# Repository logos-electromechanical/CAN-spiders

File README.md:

# CAN-spiders
A set of small single-function CAN nodes

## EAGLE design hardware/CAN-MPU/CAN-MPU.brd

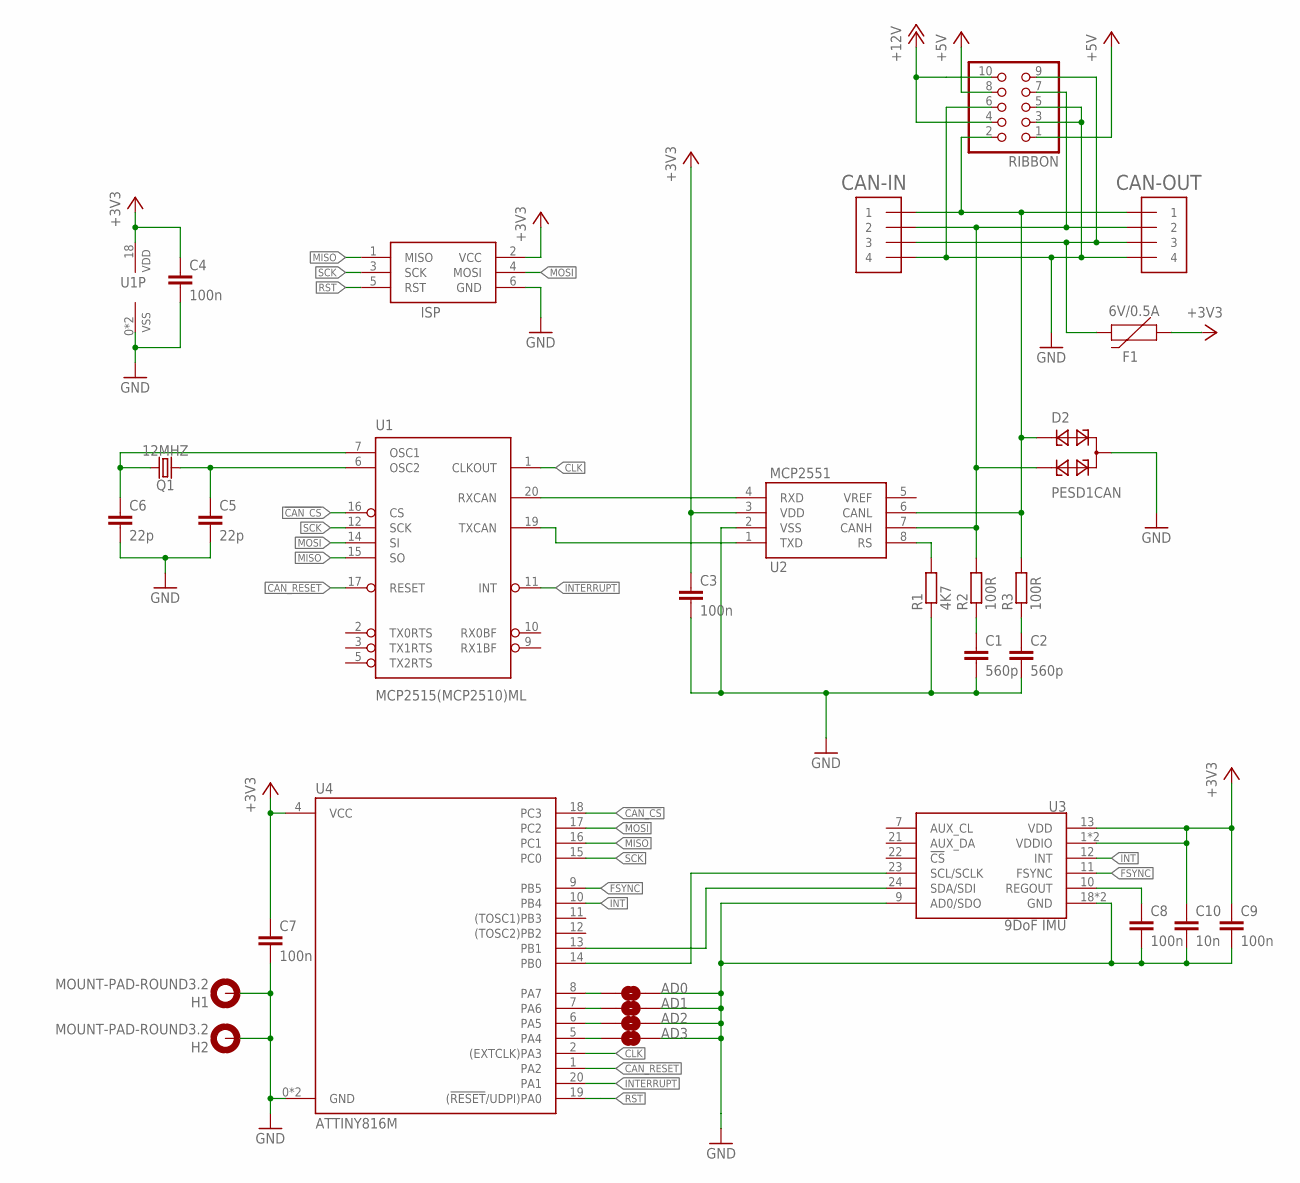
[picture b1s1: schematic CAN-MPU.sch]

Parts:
AD0, AD1, AD2, AD3: JUMPER-SMT_2_NO_SILK; SMT-JUMPER_2_NO_SILK
C1, C2: 560p; C0603
C3, C4, C7, C8, C9: 100n; C0603
C5, C6: 22p; C0603
C10: 10n; C0603
CAN-IN: STRAWSON_EAGLE_LIB_JST_SH_4; STRAWSON_EAGLE_LIB_JST_SH_4_SMD
CAN-OUT: STRAWSON_EAGLE_LIB_JST_SH_4; STRAWSON_EAGLE_LIB_JST_SH_4_SMD
D2: PESD1CAN; SOT23
F1: 6V/0.5A; 1206
H1, H2: MOUNT-PAD-ROUND3.2; 3,2-PAD
ISP: AVRISP-6; AVRISP
Q1: 12MHZ; CRYSTAL-SMD-3.2X1.5MM
R1: 4K7; R0603
R2, R3: 100R; R0603
RIBBON: PINHD-2X5_2.54-SMD; 2X05SMD
U1: MCP2515(MCP2510)ML; QFN20
U2: MCP2551; SO08
U3: 9DoF IMU; QFN24-3X3
U4: ATTINY816M; QFN20

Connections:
!CAN_CS!: U1.16 (CS), U4.18 (PC3)
+3V3: C3.1, C4.1, C7.1, C9.1, C10.1, F1.1, ISP.2 (VCC), U1.18 (VDD), U2.3 (VDD), U3.1 (VDDIO), U3.8 (VDDIO), U3.13 (VDD), U4.4 (VCC)
+5V: RIBBON.1, RIBBON.8
+12V: RIBBON.4, RIBBON.10
CAN_RESET: U1.17 (RESET), U4.1 (PA2)
CLK: U1.1 (CLKOUT), U4.2 ((EXTCLK)PA3)
FSYNC: U3.11 (FSYNC), U4.9 (PB5)
GND: AD0.2, AD1.2, AD2.2, AD3.2, C1.2, C2.2, C3.2, C4.2, C5.2, C6.2, C7.2, C8.2, C9.2, C10.2, CAN-IN.4, CAN-OUT.4, D2.3, H1.B3,2, H2.B3,2, ISP.6 (GND), R1.1, RIBBON.3, RIBBON.5, RIBBON.6, U1.0 (VSS), U1.8 (VSS), U2.2 (VSS), U3.9 (AD0/SDO), U3.18 (GND), U3.20 (GND), U4.0 (GND), U4.3 (GND)
INT: U3.12 (INT), U4.10 (PB4)
INTERRUPT: U1.11 (INT), U4.20 (PA1)
MISO: ISP.1 (MISO), U1.15 (SO), U4.16 (PC1)
MOSI: ISP.4 (MOSI), U1.14 (SI), U4.17 (PC2)
unnamed: U1.20 (RXCAN), U2.4 (RXD)
unnamed: U1.19 (TXCAN), U2.1 (TXD)
unnamed: R1.2, U2.8 (RS)
unnamed: CAN-IN.2, CAN-OUT.2, D2.2, R2.2, RIBBON.7, U2.7 (CANH)
unnamed: CAN-IN.1, CAN-OUT.1, D2.1, R3.2, RIBBON.2, U2.6 (CANL)
unnamed: C1.1, R2.1
unnamed: C2.1, R3.1
unnamed: AD3.1, U4.5 (PA4)
unnamed: AD2.1, U4.6 (PA5)
unnamed: C6.1, Q1.P$2 (2), U1.7 (OSC1)
unnamed: C5.1, Q1.P$1 (1), U1.6 (OSC2)
unnamed: AD1.1, U4.7 (PA6)
unnamed: CAN-IN.3, CAN-OUT.3, F1.2, RIBBON.9
unnamed: AD0.1, U4.8 (PA7)
unnamed: U3.24 (SDA/SDI), U4.13 (PB1)
unnamed: U3.23 (SCL/SCLK), U4.14 (PB0)
unnamed: C8.1, U3.10 (REGOUT)
RST: ISP.5 (RST), U4.19 ((!RESET!/UDPI)PA0)
SCK: ISP.3 (SCK), U1.12 (SCK), U4.15 (PC0)

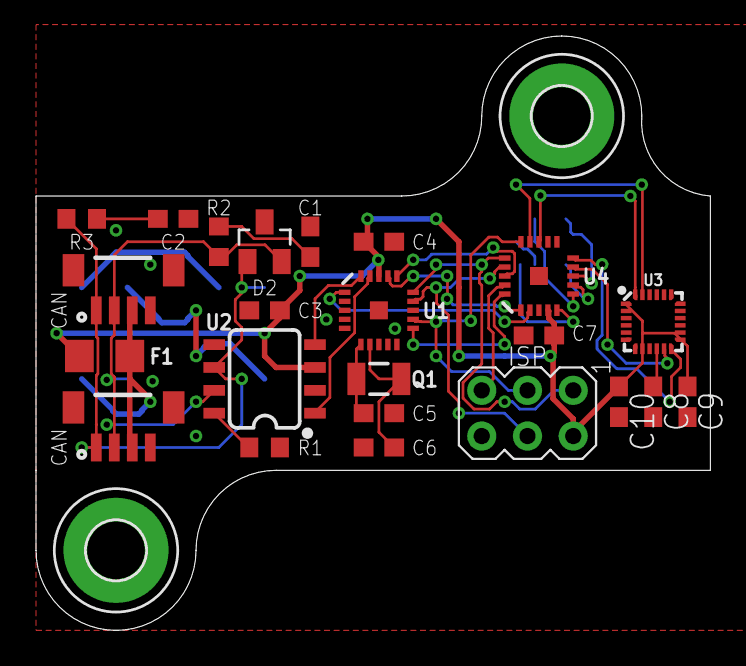
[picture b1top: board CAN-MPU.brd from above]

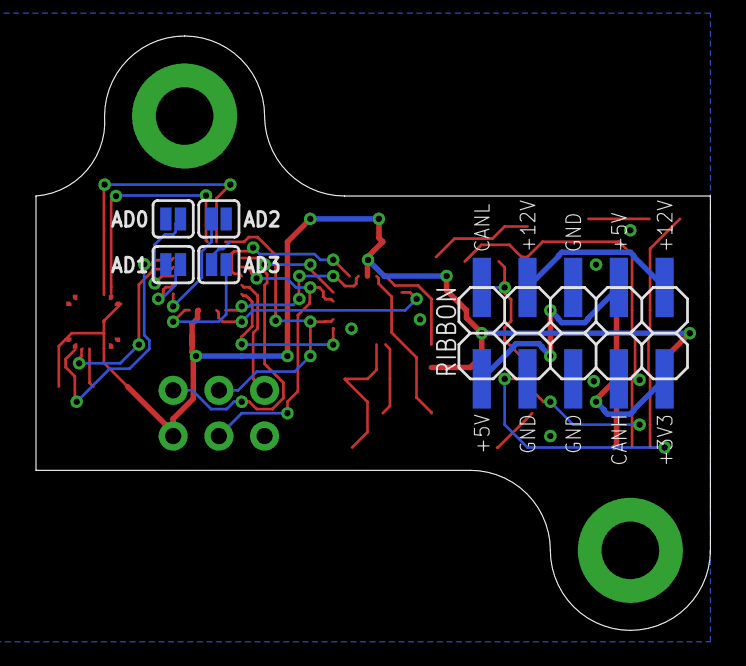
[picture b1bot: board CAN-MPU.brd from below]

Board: 2 copper layers, 37.5 x 33.0 mm, 30 parts (5 on the bottom side), 31 nets.

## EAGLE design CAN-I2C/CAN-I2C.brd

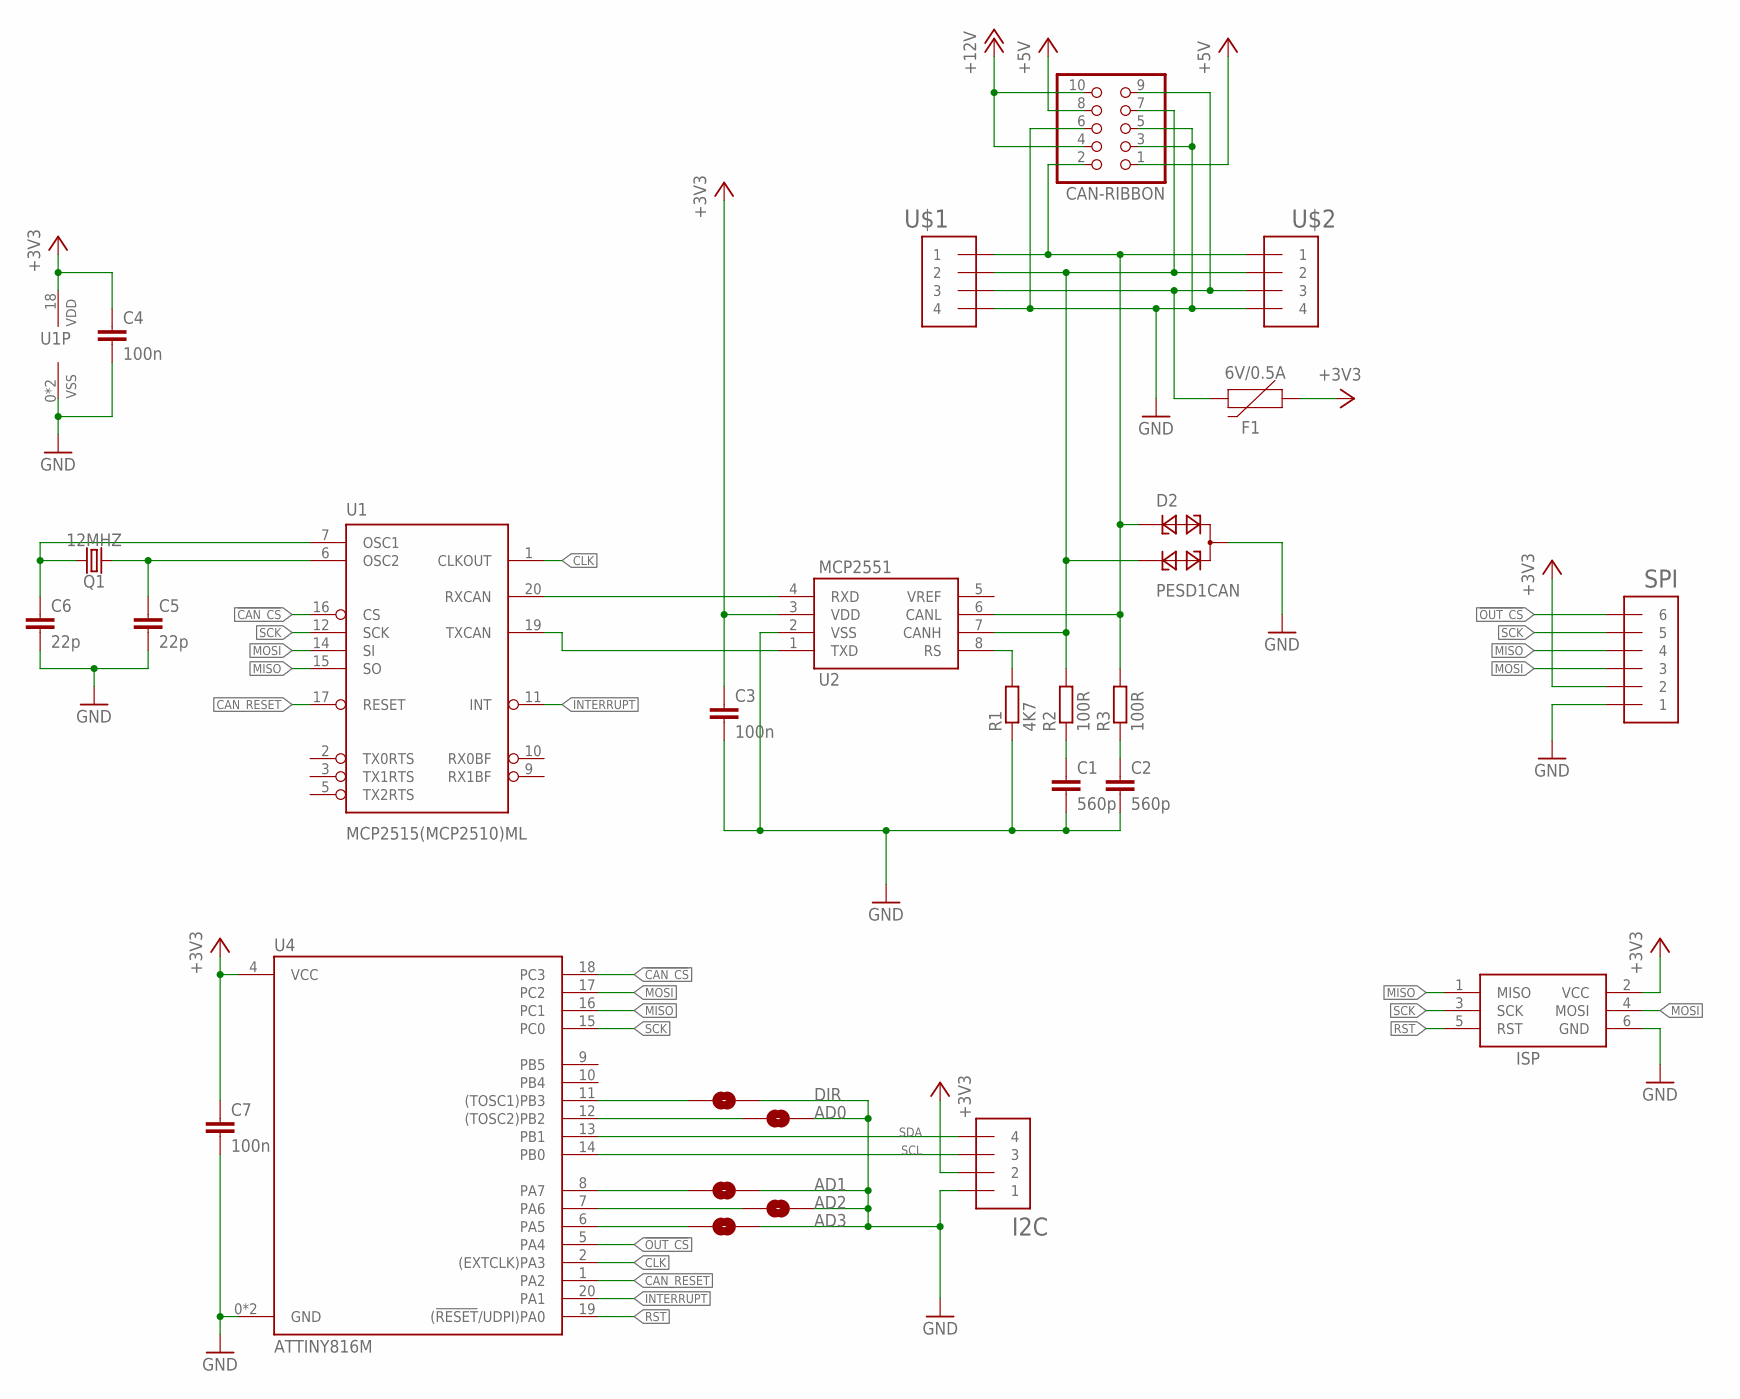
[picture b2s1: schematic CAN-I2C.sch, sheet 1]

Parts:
AD0, AD1, AD2, AD3: JUMPER-SMT_2_NO_SILK; SMT-JUMPER_2_NO_SILK
C1, C2: 560p; C0603
C3, C4, C7: 100n; C0603
C5, C6: 22p; C0603
CAN-RIBBON: PINHD-2X5_2.54-SMD; 2X05SMD
D2: PESD1CAN; SOT23
DIR: JUMPER-SMT_2_NO_SILK; SMT-JUMPER_2_NO_SILK
F1: 6V/0.5A; 1206
I2C: STRAWSON_EAGLE_LIB_JST_SH_4; STRAWSON_EAGLE_LIB_JST_SH_4_SMD
ISP: AVRISP-6; AVRISP
Q1: 12MHZ; CRYSTAL-SMD-3.2X1.5MM
R1: 4K7; R0603
R2, R3: 100R; R0603
SPI: STRAWSON_EAGLE_LIB_JST_SH_6
U1: MCP2515(MCP2510)ML; QFN20
U2: MCP2551; SO08
U4: ATTINY816M; QFN20
U$1, U$2: STRAWSON_EAGLE_LIB_JST_SH_4; STRAWSON_EAGLE_LIB_JST_SH_4_SMD

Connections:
!CAN_CS!: U1.16 (CS), U4.18 (PC3)
!OUT_CS!: SPI.6, U4.5 (PA4); also elsewhere on the board
+3V3: C3.1, C4.1, C7.1, F1.1, I2C.2, ISP.2 (VCC), SPI.2, U1.18 (VDD), U2.3 (VDD), U4.4 (VCC); also elsewhere on the board
+5V: CAN-RIBBON.1, CAN-RIBBON.8; also elsewhere on the board
+12V: CAN-RIBBON.4, CAN-RIBBON.10; also elsewhere on the board
CAN_RESET: U1.17 (RESET), U4.1 (PA2)
CLK: U1.1 (CLKOUT), U4.2 ((EXTCLK)PA3)
GND: AD0.2, AD1.2, AD2.2, AD3.2, C1.2, C2.2, C3.2, C4.2, C5.2, C6.2, C7.2, CAN-RIBBON.3, CAN-RIBBON.5, CAN-RIBBON.6, D2.3, DIR.2, I2C.1, ISP.6 (GND), R1.1, SPI.1, U1.0 (VSS), U1.8 (VSS), U2.2 (VSS), U4.0 (GND), U4.3 (GND), U$1.4, U$2.4; also elsewhere on the board
INTERRUPT: U1.11 (INT), U4.20 (PA1)
MISO: ISP.1 (MISO), SPI.4, U1.15 (SO), U4.16 (PC1); also elsewhere on the board
MOSI: ISP.4 (MOSI), SPI.3, U1.14 (SI), U4.17 (PC2); also elsewhere on the board
unnamed: U1.20 (RXCAN), U2.4 (RXD)
unnamed: U1.19 (TXCAN), U2.1 (TXD)
unnamed: R1.2, U2.8 (RS)
unnamed: CAN-RIBBON.7, D2.2, R2.2, U2.7 (CANH), U$1.2, U$2.2
unnamed: CAN-RIBBON.2, D2.1, R3.2, U2.6 (CANL), U$1.1, U$2.1
unnamed: C1.1, R2.1
unnamed: C2.1, R3.1
unnamed: AD1.1, U4.8 (PA7)
unnamed: DIR.1, U4.11 ((TOSC1)PB3)
unnamed: C6.1, Q1.P$2 (2), U1.7 (OSC1)
unnamed: C5.1, Q1.P$1 (1), U1.6 (OSC2)
unnamed: AD0.1, U4.12 ((TOSC2)PB2)
unnamed: CAN-RIBBON.9, F1.2, U$1.3, U$2.3
unnamed: AD2.1, U4.7 (PA6)
unnamed: AD3.1, U4.6 (PA5)
RST: ISP.5 (RST), U4.19 ((!RESET!/UDPI)PA0)
SCK: ISP.3 (SCK), SPI.5, U1.12 (SCK), U4.15 (PC0); also elsewhere on the board
SCL: I2C.3, U4.14 (PB0); also elsewhere on the board
SDA: I2C.4, U4.13 (PB1); also elsewhere on the board

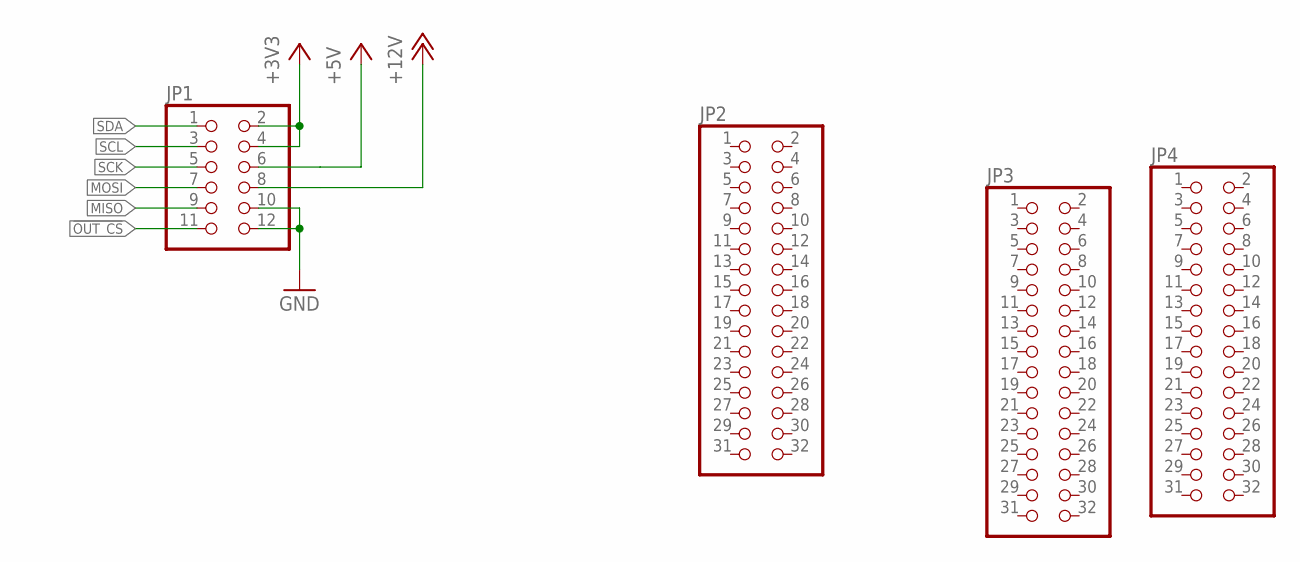
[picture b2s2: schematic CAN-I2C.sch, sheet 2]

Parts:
JP1: PINHD-2X6; 2X06
JP2, JP3, JP4: PINHD-2X16; 2X16

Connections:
!OUT_CS!: JP1.11; also elsewhere on the board
+3V3: JP1.2, JP1.4; also elsewhere on the board
+5V: JP1.6; also elsewhere on the board
+12V: JP1.8; also elsewhere on the board
GND: JP1.10, JP1.12; also elsewhere on the board
MISO: JP1.9; also elsewhere on the board
MOSI: JP1.7; also elsewhere on the board
SCK: JP1.5; also elsewhere on the board
SCL: JP1.3; also elsewhere on the board
SDA: JP1.1; also elsewhere on the board

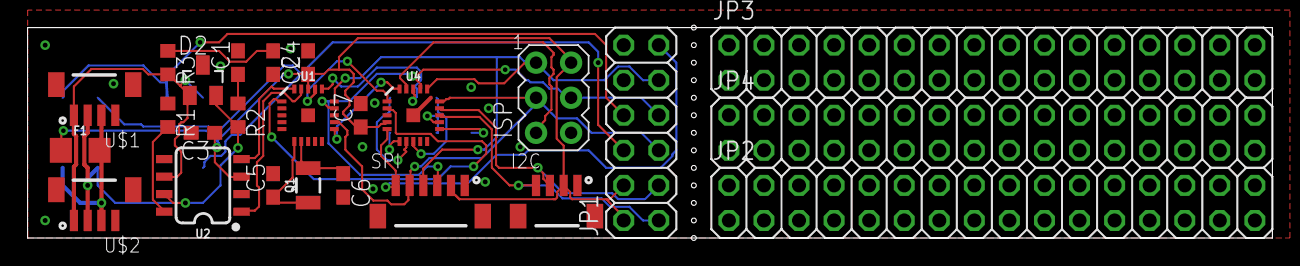
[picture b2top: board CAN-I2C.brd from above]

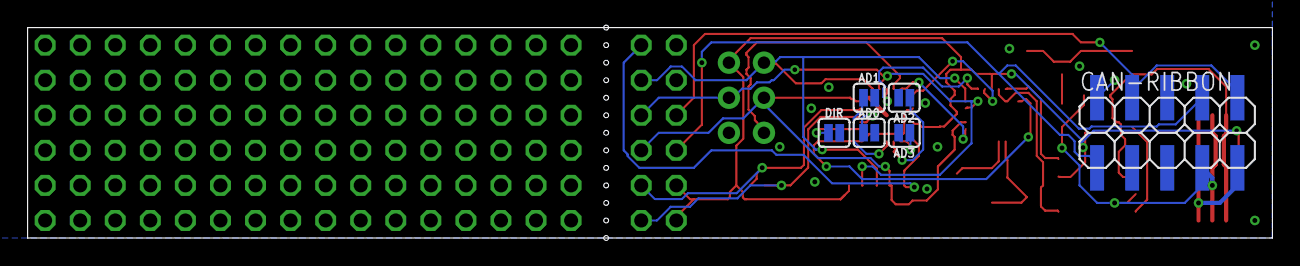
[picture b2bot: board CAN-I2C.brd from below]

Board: 2 copper layers, 90.2 x 15.2 mm, 31 parts (6 on the bottom side), 30 nets.

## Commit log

2018-08-03 Initial commit of I2C/SPI board
2018-08-06 Re-arranging directory structure
2018-08-06 Silkscreen and routing cleanup
2018-08-06 Added RAMPS carrier board
2018-08-07 Added mounting tabs
2018-08-07 Added MPU-9250 board

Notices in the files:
parts and their libraries:
SparkFun-Jumpers: Licensing: Creative Commons ShareAlike 4.0 International - https://creativecommons.org/licenses/by-sa/4.0
